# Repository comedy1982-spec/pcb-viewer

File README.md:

# AllinOneDesign

**요구사항 한 줄에서 시스템 다이어그램 → 회로 → PCB → 기구(하우징)까지, 브라우저 하나에서 AI와 함께 설계하는 단일 HTML 도구**입니다. 파일은 브라우저 안에서만 처리되며 서버로 전송되지 않습니다.

- 실행: `dist/index.html`을 브라우저로 엽니다 (3D·zip·엑셀 라이브러리만 CDN에서 불러오므로 인터넷 연결 필요).
- 사용 설명서: [docs/manual.html](docs/manual.html) · 기능 상세 노트(버전별): [docs/DETAILS.md](docs/DETAILS.md)
- 예제: SENSE-32, MCU DC 모터(MOTION-32 DEV), MCU BLDC 3상(MOTION-32 BLDC), AURIX TC364 인버터 — 첫 화면의 예제 칩으로 엽니다.

## 주요 기능

### 1. 단계별 설계 (신규 설계)
| 단계 | 하는 일 | 결과물 |
|---|---|---|
| **1 시스템 다이어그램** | 프로젝트 이름·요구사항을 적으면 AI가 분석하고, 빠진 필수 정보(전원·MCU·통신·기능·환경)는 **응답형 질문 카드**로 물어본 뒤 HW 블록 다이어그램을 그립니다. 블록·기능·인터페이스를 명령 또는 패널에서 편집합니다. | HW 블록 다이어그램 (SVG) |
| **2 회로** | 다이어그램을 **저가형 · 표준 · 확장형** 세 회로 안으로 풀어 BOM 참고가·부품 수·여유 MCU 핀·레귤레이터 손실·점수를 비교하고 하나를 고릅니다. 실제 부품 선정 · 넷리스트 · MCU 핀 배정 · 회로도가 만들어지며, **데이터시트 탭**에서 부품별 정리 페이지(HTML DB)를 봅니다. | 회로도(여러 시트) · 넷리스트 · BOM |
| **3 PCB** | 층 수(2–10) · 보드 크기(최소화/자동/직접) · 배치 전략을 고르면 자동 배치·배선합니다. 부품 끌어 옮기기·배선·비아·DRC·래츠네스트 편집, 내층을 포함한 **층별 보기**, 핀 스왑으로 회로와 함께 수정. | 배치·배선된 보드 (KiCad 저장) |
| **모터 파워 스테이지** | DC 모터 H-브리지(게이트 드라이버 ×2 + 외부 N-MOSFET ×4)·3상 인버터(×3 + ×6)를 전류 등급에 맞춰 FET 병렬·션트·전류 앰프·벌크·역전압 P-FET까지 회로로 생성, 트레이스 폭에 모터 전류 반영. | 회로도 · BOM |
| **부품 핀** | 라이브러리에 핀이 없으면 데이터시트 PDF를 올려 핀 표를 읽어 저장(pdf.js, 패키지별 표 선택, AI 모드 Claude 판독) — `datasheet <MPN>`, add part / replace, 라이브러리 버튼. | 핀 배열 → 회로 |
| **1 안전 목표** | ASIL ≠ QM이면 안전 목표(SG)를 고르고 위반 경로 블록에 태그, 구조 변형 3안(단일 MCU+외부 감시 · 메인+세이프티 MCU · ASIL 분해 2채널)을 DC·FTTI·원가로 비교해 적용, 규칙으로 검증(감지·독립 차단·FTTI·독립성·공통 원인). | SG 태그 · 검증 ✓/✗ |
| **4 기구 CAD** | 보드를 감싸는 보호 하우징을 Text-to-CAD로 설계합니다(시안 A 다이캐스팅·B 사출 스냅핏·C 압출 프로파일·D 하이브리드, 재질 6종·IP·진동·발열 조건, 구멍·글랜드·벤트·탭·리브·핀·각인, 둥근모따기/각모따기). 3D에서 요소를 **선택해 AI에게 지시**하고, 조립도·부품도(베이스/커버)·기구 BOM·SCAD/STL을 냅니다. | 하우징 3D · 도면 · BOM · SCAD |

기존 프로젝트(KiCad `.kicad_pcb`·회로도, PADS Logic 회로도, Gerber, 뷰어 JSON)도 같은 단계 표시줄로 오갑니다. 1단계는 보드에서 추출한 HW 블록 다이어그램입니다.

### 2. AI 설계 도우미
- 오른쪽 도킹 패널의 **설계 도우미**가 네 단계의 콘솔(시스템·회로도·배치/배선·Text-to-CAD)을 하나의 대화로 합칩니다. 결정론 모드는 문장을 규칙으로 명령으로 바꾸고, AI 모드는 Claude가 같은 명령을 골라 실행합니다.
- 설계를 바꾼 실행마다 **변경 요청 카드**가 붙습니다: 시스템·회로·PCB·HSIS·기구·BOM 영향, 변경 요약, 실행한 명령. **승인**하면 `CR-n` 리비전으로 기록되고, **되돌리기**는 그 실행만 정확히 되돌립니다.
- 기구 CAD에서는 3D나 형상 트리에서 요소를 고른 뒤(Shift/Ctrl 다중) "이거 M20으로 키우고 윗면은 R2"처럼 지시합니다.
- **등급 부품 자동 적용**: ASIL 프로젝트는 회로 생성 때 상용 부품을 핀 호환 차량용(AEC-Q100/Q101/Q200) 부품으로 바꾸고, `safety parts [--apply]`가 등급 미달·미상 부품과 대체품을 점검·일괄 교체합니다. 부품 레코드에 등급·온도·ASIL·FIT 필드(CSV·Claude 추정·API).
- **기능 안전(ASIL)**: 요구사항의 ASIL A~D를 읽어 시스템·블록 등급(배지·세이프 스테이트 경로·FFI 경계)을 다이어그램에 얹고, 등급별 권장 안전 메커니즘(전원 감시·외부 워치독·fault 리드백·SBC·이중 차단·리던던트 센서·2채널)을 블록으로 추가해 회로 부품(TPS3823 감시/워치독, 하이사이드 차단 스위치)까지 생성합니다. 회로·PCB 콘솔 `safety check`/`safety fmeda`가 등급별 회로 점검과 FIT·DC·SPFM·PMHF 추정을 내고 보고서·Excel·HSIS에 실립니다.
- **회로 해석(analyze)**: 전원 트리 · 디커플링 감사 · RC/LC·분압·LED 패턴 · 수동 소자 AC 주파수 응답 · DC 동작점(MNA) · IR drop · 신호 무결성 · 열 · EMC를 조회 명령으로 열어, 질문 모드의 Claude가 "필터 컷오프 얼마야?", "레일 전압 강하는?"에 계산값으로 답합니다.
- **아무 부품이나 추가**: "CC2420 추가해줘" → 라이브러리/Claude 추정의 핀 배열로 심볼을 만들고 전원·접지 자동 연결, 나머지 핀은 `connect`로, `apply`로 보드에(패키지 이름으로 풋프린트 생성).
- **보드 모양**: 사각형 외에 라운드·원형·타원·L자·T자·육각·팔각·다각형과 컷아웃(구멍) — 시작 카드에서 고르거나 `board shape …`/"원형 60mm로".
- **제품 프로필**: "EPS ECU 설계"처럼 제품만 적어도 표준 블록 구성(전원·SBC·락스텝 MCU·CAN-FD·인버터·페이즈 컷·센서 IF…)을 먼저 깔고, 블록별로 갈리는 것(타입·센서 IF·리던던시…)만 묻습니다. AI 모드는 어떤 제품이든, 규칙 모드는 EPS·BMS·BCM·인버터 템플릿.
- **로컬 AI**: claude.ai 밖(내려받은 파일·`npm run serve`)에서는 [Claude 허용] → 로컬 AI 설정에 API 키(또는 프록시)를 넣으면 같은 AI 모드가 Messages API로 동작합니다. `npm run serve:copilot`이면 API 키 없이 **GitHub Copilot** 구독(Copilot CLI 로그인)으로 동작합니다.
- **회로 보강 명령**: "HSIS 기준으로 테스트 포인트 전부 달아줘"(`tp`), "안 쓰는 핀 10k로 GND에"(`tie`), "전원 입력에 페라이트 비드"(`insert`), `add C --pins U1.12,GND`처럼 핀을 직접 지정 — AI 모드가 이 명령들로 풀어 실행하고 보드에 반영(`apply`)까지 합니다. TP는 HSIS 표의 TP 열·검사에 연결됩니다.
- **부품 교체(대화형)**: "U2를 AP2112K-3.3으로 바꿔줘"라고 하면 승인 부품 목록 → 내장 DB → Claude 추정 → 부품 API(Mouser·Nexar·사내 서버) 순으로 부품을 찾고, 핀 대응(이름·역할·번호)을 표로 확인받은 뒤 회로도·보드(풋프린트 자동 생성)·BOM·데이터시트·HSIS를 한 번에 바꿉니다. 머리글 **부품** 창에서 회사 승인 부품 목록(CSV/Excel)을 가져오고 추정 결과를 승인·내보냅니다.

### 3. 보기 · 분석
- **3D / TOP / BOTTOM / 층별(내층 포함) / 회로도**, 나란히 보기, 여러 보기를 격자로 띄우는 **새 창**(시스템 다이어그램·기구 3D·기구 도면·HSIS·시뮬레이션 포함, 메인 창과 연동).
- **지표 띠**: BOM 참고가, 가이드라인 점수, DRC·미배선, HSIS 정상/전체, 최고 Tj, 하우징 무게·IP — 누르면 해당 화면으로.
- **전체 보기**: 네 단계의 그림과 수치가 화살표로 이어진 한 화면, AI 바 포함.
- **시뮬레이션**: 전압 강하(IR drop), 신호 무결성, 열 분포, EMC/EMI, 회로 동작(MNA + 펌웨어 코시뮬레이션: LED·모터가 3D에서 움직임).
- **설계 가이드라인** 점검(회로·PCB 프리셋), DRC.

### 4. HSIS (HW/SW 인터페이스 사양)
- 엑셀 HSIS와 AUTOSAR ARXML을 읽어 **신호 표 · MCU 핀 맵 · 추적성(요구사항↔테스트) · 검사 결과 · 핀 추천(헝가리안 매칭) · MCAL 설정 · 테스트 케이스(SWE.6/SYS.4)**를 만들고 회로도·보드·펌웨어와 대조합니다.
- 보드에 HSIS가 없으면 MCU 핀과 넷으로 초안을 만듭니다.

### 5. 멀티보드 시스템
- 메인 + 센서 보드처럼 **보드 둘 이상을 커넥터로 잇는 제품**을 한 시스템으로 묶습니다. 머리글의 보드 선택 상자로 보드를 추가(파일·신규 설계·예제)하고 오갑니다.
- **시스템 연결** 탭: 보드·커넥터 짝으로 연결(케이블/B2B)을 만들고 핀을 번호·넷 이름·직접으로 매핑, 핀 수·짝 없는 핀·접지/전원/신호 충돌·레일 전압·차동 쌍 점검, 보드 연결도(SVG/PNG), 시스템 넷, 시스템 BOM(보드별 수량) → Excel·보고서.

### 6. 리비전 기록 · 비교
- 설계가 바뀌면 자동으로 리비전이 쌓이고(원인·단계·변경 요약 포함), 이름·단계(Proto~MP)·메모를 붙여 저장할 수 있습니다.
- **비교**: 요약 · 부품 · 배치 · 넷/핀 · **PCB 겹쳐 보기**(같음/A에만/B에만) · 다이어그램·계획 · HSIS · 기구. **원장** 보기는 리비전×영역 표.
- **복원**, 이력 JSON 내보내기/불러오기(Git에 함께 커밋).

### 7. 내보내기
- **프로젝트 저장 · 열기 · 이어서 하기**: 설계 중 어느 단계에서든 [저장](Ctrl+S)으로 전체 설계(모든 보드 · 요구사항 · 다이어그램 · 회로 안 · PCB · 기구 · HSIS, 열려 있던 단계)를 `.aod.json` 한 파일로 받고, [열기](Ctrl+O) · 첫 화면 · 파일 불러오기로 다시 엽니다. 작업은 브라우저에도 자동 저장돼, 새로 고침 뒤 첫 화면의 [이어서 하기]로 돌아옵니다.
- 회로도 교환: **PADS Logic ASCII**(.txt) 내보내기·가져오기, PADS Layout용 **PADS 넷리스트**(.asc), KiCad `.kicad_sch`. 회로도 파일만 넣으면 그 부품·넷으로 보드를 만들어 PCB 단계로 이어 갑니다.
- 그림: 2D 보드(층별)·회로도는 화면과 동일한 **SVG**, PNG, 시스템 다이어그램, 3D·기구 3D PNG, 기구 조립도·부품도, 모든 층 zip.
- 표: HSIS(시트별), BOM, 부품 배치, 넷리스트, 층 구성, 기구 BOM, 리비전 기록, 비교 결과 → **Excel**.
- **설계 보고서**: 항목을 골라 그림·표를 모두 담은 HTML 한 파일(브라우저 인쇄로 PDF). KiCad PCB/회로도 저장, OpenSCAD·STEP(AP214 솔리드 — SolidCraft·Fusion·SolidWorks·FreeCAD)·STL·HSIS CSV·MCAL 파일.

### 8. 실제 부품 데이터
- 부품 DB(제조사·사양·데이터시트 링크·참고 단가)와 MCU 핀 기능 DB(TC364DP, STM32F042), 부품당 한 레코드인 **데이터시트 DB**(원본 `datasheets/records/*.json` → 페이지 `datasheets/db/`, `npm run dsdb`; 회로 생성기의 후보 사양도 여기서 읽음).
- **부품 라이브러리**: 승인 부품 목록(CSV/Excel) · Claude 추정 · 부품 API 결과를 브라우저에 쌓아 두고 교체·데이터시트 탭에서 씁니다. 패키지 이름만으로 풋프린트(SOT-23-5, SOIC-14, QFN-24 4x4, DIP-8 …)를 만들어 보드에 올립니다.

## 화면 구성

```
┌ 머리: 프로젝트 · [전체] [1 시스템 · 2 회로 · 3 PCB · 4 기구] [HSIS] [시스템 연결] · 불러오기 · 내보내기 · 리비전 · 보기 전환 · 도우미 ┐
├ 지표 띠: BOM · 가이드라인 · DRC · HSIS · 최고 Tj · 시스템 연결 · 하우징                                                       ┤
├ 작업 공간 (단계마다 바뀜)                                            │ 도킹 패널: 설계 도우미 · 정보 · 시뮬레이션 · 데이터시트 ┤
│   레이어/보드 요약 · 3D/TOP/BOTTOM/층별/회로도 · 시스템 다이어그램 · 기구 CAD · HSIS │   (탭마다 새 창으로 뗄 수 있음)              │
└──────────────────────────────────────────────────────────────────┴──────────────────────────────────────────────┘
```

## 개발

```sh
npm run build     # src/ → dist/index.html (datasheets/db → dsdb.js 포함, Node 18+)
npm test          # 파서·회로도·시뮬레이션·HSIS·배치·배선·하우징·리비전·내보내기 테스트
npm run dsdb      # 데이터시트 HTML DB 번들 · npm run dsdb:init 초안 생성
npm run examples  # examples/ 다시 만들기 (python3 + openpyxl)
```

| 경로 | 내용 |
|---|---|
| `src/core/` | 보드 모델·파서(`pcb-core`), 편집(`pcbedit`), 자동 배치(`autoplace`), HW 아키텍처(`hwarch`), 시스템 다이어그램(`sysdiag`), 새 회로 설계(`newproj`), 하우징(`housing`), Text-to-CAD(`text2cad`), 가이드라인(`guide`), 리비전 스냅샷·비교(`revlog`), 멀티보드 시스템(`multiboard`), 부품 라이브러리·핀 대응(`partlib`), 풋프린트 생성(`fpgen`) |
| `src/route/autoroute.js` | 다층 자동 배선 |
| `src/sch/` | 회로도 파서·생성·편집 (KiCad, PADS Logic `pads.js`) |
| `src/sim/` | 전기·열·EMC 해석, MNA 회로 해석 |
| `src/hsis/` | HSIS 파서·검사·추적성, 핀 추천, MCAL, 테스트 케이스 생성 |
| `src/parts/` | 부품 DB, MCU 핀 DB, 데이터시트 DB 번들 |
| `src/fw/fw.js` | MCU 펌웨어 런타임 (샌드박스, 회로와 1 ms 코시뮬레이션) |
| `src/app/` | 화면: `viewer`(2D/3D), `newui`(단계·회로 안), `copilot`(도우미), `pcbui`·`pcbcli`(PCB 편집·CLI), `schui`·`schcli`, `mechui`(기구), `hsisui`, `simui`, `popui`(새 창), `exportui`, `revui`, `nextui`(지표·전체 보기·변경 요청·원장·분해), `iconui`, `mbui`(멀티보드), `partui`(부품 교체·라이브러리), `modeui`, `dsui`, `aimode` |
| `datasheets/records/` | 부품별 데이터시트 레코드(JSON, 원본) |
| `datasheets/db/` | 레코드에서 생성한 HTML 페이지 |
| `docs/` | 사용 설명서(`manual.html`), 기능 상세 노트(`DETAILS.md`), 화면 캡처(`img/`) |
| `test/` | `node --test` 테스트 |

모든 수치(열·진동·EMC·단가·하우징)는 초기 설계용 추정입니다. 양산 전에는 전문 도구와 시험으로 확인하세요.

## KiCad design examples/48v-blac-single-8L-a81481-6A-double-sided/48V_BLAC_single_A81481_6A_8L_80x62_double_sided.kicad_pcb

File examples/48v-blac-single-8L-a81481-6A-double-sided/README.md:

# 48 V BLAC 단일 채널 · A81481 · 6 A · 8층 80 × 62 mm (양면 배치)

[6 A 단면 예제(84 × 66)](../48v-blac-single-8L-a81481-6A/)와 같은 회로를 양면으로 배치한 보드입니다. 부품 113개 중 29개(전원 · MCU · 통신 · 센싱 쪽 패시브와 소형 IC)가 아랫면에 있고, FET · 게이트 드라이버 · 커넥터는 윗면에 있습니다. 면적은 단면 대비 −10.5 %입니다.

> A81481은 출시 전 부품이라 핀 배치가 **가정**입니다. 그대로 출도할 수 없습니다.

## 결과
- 미연결 0 · DRC 0 · 비아 전류 미달 없음
- 상 폭 PH_U 9.83 · PH_V 12.15 · PH_W 12.78 mm (필요 1.17 mm), 평면 온도 상승 +48 V +1.4 °C · GND +0.4 °C
- 미세 피치 IC 반대면 바로 아래에는 부품이 없습니다

## 더 작은 크기 (양면 · 시드 1)
78 × 62 미연결 1 · 80 × 60 미연결 2 · 78 × 60 미연결 2 · 76 × 62 미연결 3과 간격 오류 1 · 76 × 60 미연결 5 · 80 × 58 미연결 15.

## 만든 방법 (v1.136.0)
```
node scripts/pcbrun.cjs --plan examples/48v-blac-single-8L-a81481-6A-double-sided/plan.json --w 80 --h 62 --snap --kicad --shots \
  --cmds "board layers 8; board size 80 62 --anchor center; reset --strategy compact --both --seed 1; route; route --ai --agents --rules --noRoute --steps 12"
```
자동 배선 후 신호 2건이 남았고 오케스트레이션(규칙 처방)이 3단계에 이었습니다.

앱에서는 [파일 불러오기] → "예제: 48 V BLAC 단일 · 6 A 양면 80 × 62".

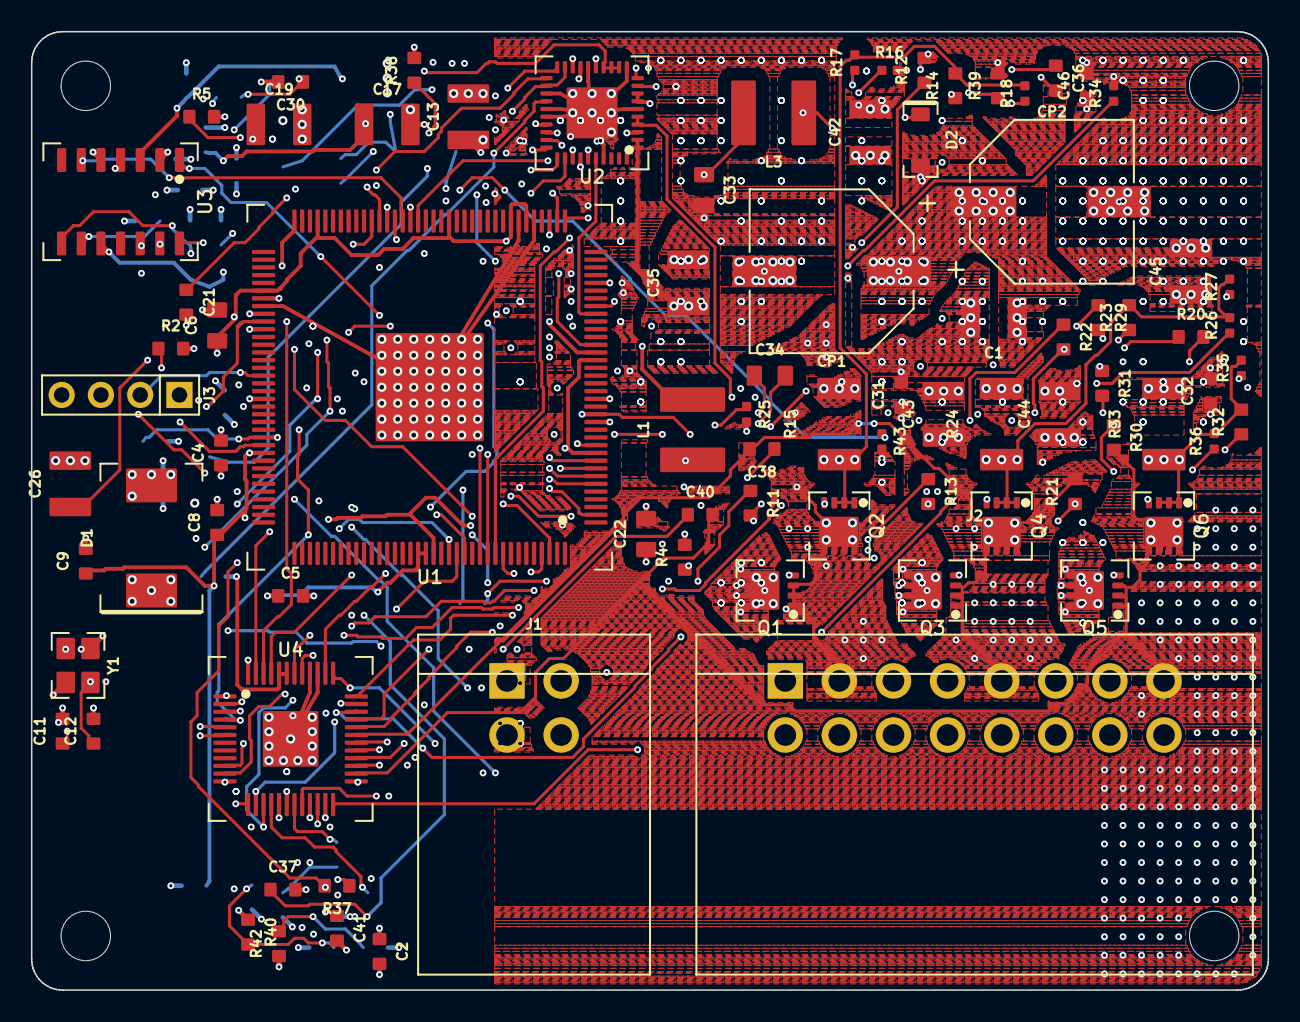
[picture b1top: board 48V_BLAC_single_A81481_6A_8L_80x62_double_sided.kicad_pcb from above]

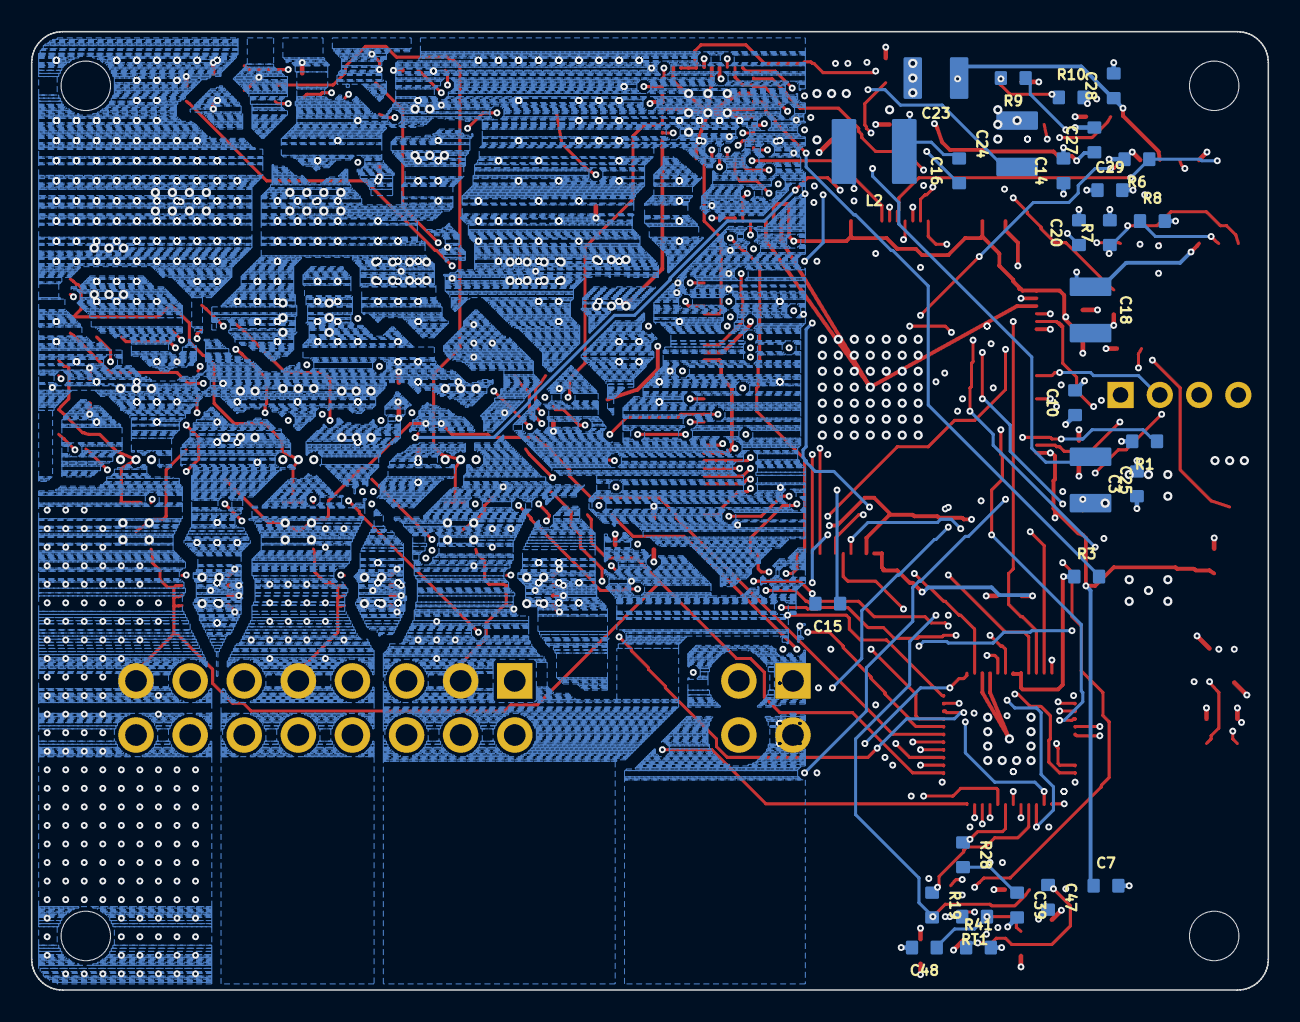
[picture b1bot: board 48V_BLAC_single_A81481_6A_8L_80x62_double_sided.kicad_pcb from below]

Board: 8 copper layers, 80.0 x 62.0 mm, 117 parts (29 on the bottom side), 95 nets.

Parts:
C1, C23, C24, C25, C26, C42, C43, C44, C45: 2.2µF; 1210
C2, C3, C4, C5, C7, C8, C10, C14, C15, C16, C20, C27, C28, C29, C31, C32, C46, C47, C48: 100nF; 0603
C6, C22, C33: 10µF; 0805
C9: 470nF; 0603
C11, C12: 12pF; 0603
C13, C35: 4.7µF; 1210
C17, C18: 10µF; 1210
C19: 22µF; 1210
C21: 1µF; 0603
C30: 4.7nF; 0603
C34: 1µF; 0805
C36, C38, C40: 68nF; 0603
C37, C39, C41: 1nF; 0603
CP1, CP2: 100µF; CP-SMD-10x10
D1: SMCJ58A; SMC
D2: PMEG10010ELR; SOD-123
H1, H2, H3, H4: MountingHole
J1: ECU-IN; MX150-2x2-RA
J2: ECU-OUT; MX150-2x8-RA
J3: DAP; HDR-1x4
L1: 22µH; IND-5x5
L2: 4.7µH; IND-5x5
L3: 100µH; IND-5x5
Q1, Q2, Q3, Q4, Q5, Q6: NVTFS6H850N; WDFN8-3.3-FET
R1, R2, R4, R5, R6, R7, R8, R12, R14, R21, R23, R30, R32, R38, R39, R42: 10kΩ; 0603
R3, R40: 100kΩ; 0603
R9, R10: 60.4Ω; 0603
R11, R13, R20, R22, R29, R31: 10Ω; 0603
R15, R24, R33: 10mΩ; 2010
R16, R17, R18, R25, R26, R27, R34, R35, R36: 0Ω; 0402
R19, R28, R37: 1kΩ; 0603
R41: 22kΩ; 0603
R43: 10kΩ; 0402
RT1: NTC 10k; 0603
U1: TC364DP; TQFP-144
U2: A81481; QFN-40
U3: TCAN1043HDRQ1; SOIC-14
U4: AMT49100; QFP-48-EP-7x7-P0.5
Y1: 20MHz; XTAL-3225

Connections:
+3V3: C3.1, C4.1, C5.1, C6.1, C10.1, C22.1, C29.1, J3.1 (3V3), R1.2, R2.2, R4.2, R5.2, R7.2, R38.2, R42.1, U1.23 (VEXT), U1.42 (VAREF1), U1.44 (VDDM), U1.52 (VEVRSB), U1.69 (VEXT), U1.78 (VEXT), U1.83 (VEXT), U1.125 (VEXT), U1.126 (VDDP3), U2.15 (VUC), U3.5 (VIO)
+5V: C23.1, C28.1, U2.17 (VLDOA), U3.3 (VCC)
+12V: C17.1, C18.1, C27.1, L1.2, U2.7 (VREG1), U2.8 (VIN2), U3.10 (VSUP)
+48V: C1.1, C2.1, C13.1, C14.1, C31.1, C32.1, C35.1, C42.1, C43.1, C44.1, C45.1, C46.1, CP1.1, CP2.1, D1.1 (K), J1.1 (BAT), Q1.5 (D), Q1.6 (D), Q1.7 (D), Q1.8 (D), Q1.9 (D), Q3.5 (D), Q3.6 (D), Q3.7 (D), Q3.8 (D), Q3.9 (D), Q5.5 (D), Q5.6 (D), Q5.7 (D), Q5.8 (D), Q5.9 (D), R3.1, R40.1, U2.1 (VIN), U2.2 (VIN), U4.43 (VBRG), U4.44 (VBB)
CANH: J1.2 (CAN_H), R9.1, U3.13 (CANH)
CANL: J1.4 (CAN_L), R10.2, U3.12 (CANL)
CAN_EN: R6.1, U1.58 (P33.2), U3.6 (EN)
CAN_ERR: R7.1, U1.142 (P10.3), U3.8 (~FAULT)
CAN_RX: U1.129 (P13.1), U3.4 (RXD)
CAN_SPLIT: C30.1, R9.2, R10.1
CAN_STB: U1.59 (P33.3), U3.14 (~STB)
CAN_TX: U1.11 (P00.0), U3.1 (TXD)
CAN_WAKE: R8.1, U3.9 (WAKE)
ESR0: R2.1, U1.98 (ESR0)
GND: C1.2, C2.2, C3.2, C4.2, C5.2, C6.2, C7.2, C8.2, C9.2, C10.2, C11.2, C12.2, C13.2, C14.2, C17.2, C18.2, C19.2, C20.2, C21.2, C22.2, C23.2, C24.2, C25.2, C26.2, C27.2, C28.2, C29.2, C30.2, C31.2, C32.2, C33.2, C35.2, C37.2, C39.2, C41.2, C42.2, C43.2, C44.2, C45.2, C46.2, C47.2, C48.2, CP1.2, CP2.2, D1.2 (A), D2.2 (A), J1.3 (GND), J3.4 (GND), R6.2, R8.2, R15.2, R16.2, R24.2, R25.2, R33.2, R34.2, R39.2, R41.2, R43.2, RT1.2, U1.41 (VAGND1), U1.43 (VSSM), U1.80 (VSS), U1.145 (VSS (노출 패드)), U2.6 (PGND1), U2.11 (PGND2), U2.16 (VUCSEL), U2.23 (AGND), U2.25 (ENCAN), U2.26 (EN), U2.37 (GND), U2.41 (GND (노출 패드)), U3.2 (GND), U4.39 (GND), U4.40 (GND), U4.49 (PAD), Y1.2, Y1.4
PH_CP1: C34.1, U4.42 (CP1)
PH_CP2: C34.2, U4.41 (CP2)
PH_DIAG: R38.1, U1.2 (P02.1), U4.6 (DIAG)
PH_EN: R39.1, U1.60 (P33.4), U4.46 (ENABLE)
PH_INH_U: U1.131 (P13.3), U4.45 (HA)
PH_INH_V: U1.130 (P13.2), U4.2 (HB)
PH_INH_W: U1.14 (P00.3), U4.4 (HC)
PH_INL_U: U1.9 (P02.8), U4.1 (LA)
PH_INL_V: U1.136 (P11.8), U4.3 (LB)
PH_INL_W: U1.17 (P00.6), U4.5 (LC)
PH_ISNS_U: C37.1, R19.2, U1.29 (AN34)
PH_ISNS_U_AMP: R19.1, U4.16 (CS1O)
PH_ISNS_V: C39.1, R28.2, U1.32 (AN28)
PH_ISNS_V_AMP: R28.1, U4.19 (CS2O)
PH_ISNS_W: C41.1, R37.2, U1.37 (AN21)
PH_ISNS_W_AMP: R37.1, U4.22 (CS3O)
PH_LX: D2.1 (K), L3.1, U4.48 (LX)
PH_RESETN: R43.1, U1.61 (P33.5), U4.47 (RESETn)
PH_SCK: U1.8 (P02.7), U4.12 (SCK)
PH_SDI: U1.7 (P02.6), U4.11 (SDI)
PH_SDO: U1.6 (P02.5), U4.10 (SDO)
PH_STRN: U1.62 (P33.6), U4.13 (STRn)
PH_U: C36.2, J2.2 (U), Q1.1 (S), Q1.2 (S), Q1.3 (S), Q2.5 (D), Q2.6 (D), Q2.7 (D), Q2.8 (D), Q2.9 (D), R12.2, U4.36 (SA)
PH_U_HG: Q1.4 (G), R11.2, R12.1
PH_U_HO: R11.1, U4.37 (GHA)
PH_U_LG: Q2.4 (G), R13.2, R14.1
PH_U_LO: R13.1, U4.34 (GLA)
PH_U_LSS: R18.1, U4.33 (LSSA)
PH_U_SNS: Q2.1 (S), Q2.2 (S), Q2.3 (S), R14.2, R15.1, R17.2, R18.2
PH_U_SNSM: R16.1, U4.15 (CS1M)
PH_U_SNSP: R17.1, U4.14 (CS1P)
PH_U_VB: C36.1, U4.35 (CA)
PH_V: C38.2, J2.5 (V), Q3.1 (S), Q3.2 (S), Q3.3 (S), Q4.5 (D), Q4.6 (D), Q4.7 (D), Q4.8 (D), Q4.9 (D), R21.2, U4.31 (SB)
PH_VREG: C33.1, L3.2, U4.38 (VREG)
PH_V_HG: Q3.4 (G), R20.2, R21.1
PH_V_HO: R20.1, U4.32 (GHB)
PH_V_LG: Q4.4 (G), R22.2, R23.1
PH_V_LO: R22.1, U4.29 (GLB)
PH_V_LSS: R27.1, U4.28 (LSSB)
PH_V_SNS: Q4.1 (S), Q4.2 (S), Q4.3 (S), R23.2, R24.1, R26.2, R27.2
PH_V_SNSM: R25.1, U4.18 (CS2M)
PH_V_SNSP: R26.1, U4.17 (CS2P)
PH_V_VB: C38.1, U4.30 (CB)
PH_W: C40.2, J2.8 (W), Q5.1 (S), Q5.2 (S), Q5.3 (S), Q6.5 (D), Q6.6 (D), Q6.7 (D), Q6.8 (D), Q6.9 (D), R30.2, U4.26 (SC)
PH_W_HG: Q5.4 (G), R29.2, R30.1
PH_W_HO: R29.1, U4.27 (GHC)
PH_W_LG: Q6.4 (G), R31.2, R32.1
PH_W_LO: R31.1, U4.24 (GLC)
PH_W_LSS: R36.1, U4.23 (LSSC)
PH_W_SNS: Q6.1 (S), Q6.2 (S), Q6.3 (S), R32.2, R33.1, R35.2, R36.2
PH_W_SNSM: R34.1, U4.21 (CS3M)
PH_W_SNSP: R35.1, U4.20 (CS3P)
PH_W_VB: C40.1, U4.25 (CC)
PMIC_BOOT1: C15.1, U2.3 (BOOT1)
PMIC_BOOT2: C16.1, U2.9 (BOOT2)
PMIC_DIAG: U1.28 (AN35), U2.36 (DIAG)
PMIC_ENBAT: R3.2, U2.24 (ENBAT)
PMIC_FFN: R4.1, U1.15 (P00.4), U2.28 (FFn)
PMIC_LX1: C15.2, L1.1, U2.4 (LX1), U2.5 (LX1)
PMIC_LX2: C16.2, L2.1, U2.10 (LX2)
PMIC_POE: U1.24 (P40.9/AN39), U2.29 (POE)
PMIC_SCL: U1.134 (P11.6), U2.32 (SCK)
PMIC_SCS: U1.56 (P33.0), U2.35 (STRn)
PMIC_SDI: U1.135 (P11.9), U2.33 (SDI)
PMIC_SDO: U1.133 (P11.3), U2.34 (SDO)
PMIC_VCC: C21.1, U2.19 (VLDOBSEL), U2.22 (VCC)
PMIC_VREG2: C19.1, C20.1, L2.2, U2.12 (VREG2), U2.13 (VREGLDO), U2.14 (VUCIN)
PMIC_WDF: R5.1, U1.141 (P10.2), U2.30 (WD_Fn)
PORST: R1.1, U1.97 (PORST), U2.27 (NPOR)
TCK: J3.3 (TCK), U1.92 (TCK)
TEMP: C48.1, R42.2, RT1.1, U1.39 (AN17)
TMS: J3.2 (TMS), U1.89 (TMS)
V5P1: C25.1, U2.20 (VLDOP1)
V5P2: C26.1, U2.21 (VLDOP2)
V5_AON: C24.1, U2.18 (VLDOB)
VDD: C7.1, C8.1, C9.1, U1.10 (VDD), U1.22 (VDD), U1.72 (VDD), U1.79 (VDD), U1.99 (VDD), U1.127 (VDD)
VMON: C47.1, R40.2, R41.1, U1.38 (AN20)
WDI: U1.57 (P33.1), U2.31 (WDIN)
XTAL1: C11.1, U1.81 (XTAL1), Y1.1
XTAL2: C12.1, U1.82 (XTAL2), Y1.3

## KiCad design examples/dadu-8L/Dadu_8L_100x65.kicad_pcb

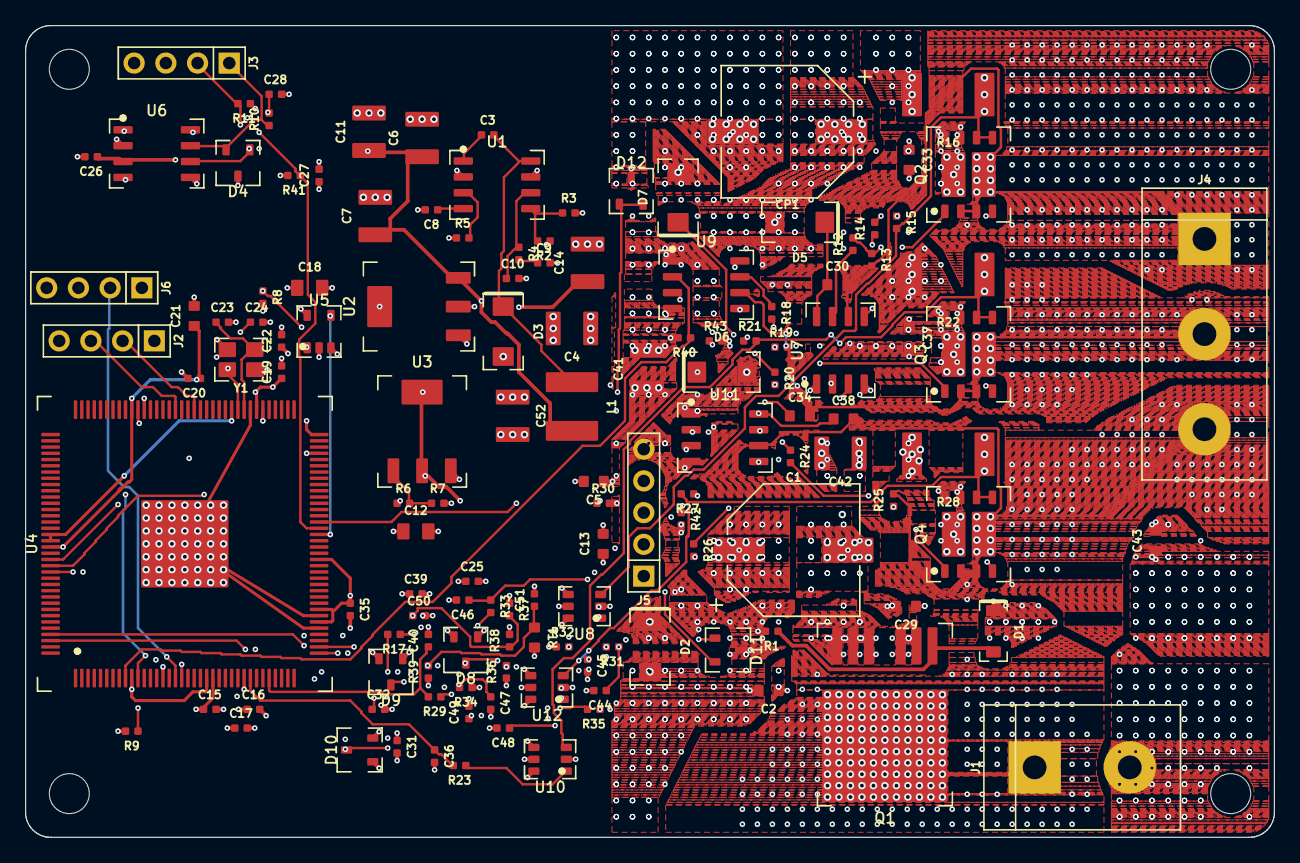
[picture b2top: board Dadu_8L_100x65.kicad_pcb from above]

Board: 8 copper layers, 100.0 x 65.0 mm, 137 parts (0 on the bottom side), 70 nets.

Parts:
C1: 470µF; CP-SMD-10x10
C2, C5, C43: 100nF; 0603
C3, C15, C16, C17, C19, C20, C22, C25, C26, C27, C31, C35, C39, C50, C51: 100nF; 0402
C4, C11, C14, C52: 10µF; 1210
C6, C7: 22µF; 1210
C8: 10nF; 0402
C9: 3.3nF; 0402
C10: 47pF; 0402
C12, C18: 10µF; 0805
C13, C29, C30, C33, C34, C37, C38: 1µF; 0603
C21: 470nF; 0603
C23, C24: 12pF; 0402
C28: 4.7nF; 0402
C32, C36, C40, C44, C45, C46, C47, C48, C49: 1nF; 0402
C41, C42: 2.2µF; 1210
CP1: 470µF; CP-SMD-10x10
D1: BZT52C12; SOD-123
D2: SMAJ15A; SMA
D3: MBRA340T3G; SMA
D4, D11, D12: PESD1CAN; SOT-23
D5, D6, D7: ES1D; SMA
D8, D9, D10: BAT54S; SOT-23
H1, H2, H3, H4: MountingHole
J1: 12V 입력; TERM-2-7.62
J2: DAP; HDR-1x4
J3: CAN; HDR-1x4
J4: 모터 상; TERM-3-7.62
J5: 홀; HDR-1x5
J6: UART; HDR-1x4
L1: 10µH; IND-5x5
Q1: IPB180P04P4L-02; TO-263-7
Q2, Q3, Q4: IAUC60N04S6N050H; TDSON-8-2FET
R1, R3, R8, R9, R13, R15, R19, R21, R25, R27, R30, R39, R40, R41, R42, R43: 10kΩ; 0402
R2: 52.3kΩ; 0402
R4: 76.8kΩ; 0402
R5, R37: 100kΩ; 0402
R6: 240Ω; 0402
R7: 1.5kΩ; 0402
R10, R11: 60.4Ω; 0402
R12, R14, R18, R20, R24, R26: 10Ω; 0402
R16, R22, R28: 2mΩ; 2512
R17, R23, R29, R31, R33, R35: 1kΩ; 0402
R32, R34, R36: 4.7kΩ; 0402
R38: 22kΩ; 0402
RT1: NTC 10k; 0603
U1: TPS54331; SOIC-8
U2: AMS1117-3.3; SOT-223
U3: LM317; SOT-223
U4: TC364DP; TQFP-144
U5: TPS3823-33; SOT-23-5
U6: TLE9251V; SOIC-8
U7, U9, U11: IR2104S; SOIC-8
U8, U10, U12: INA181A2-Q1; SOT-23-6
Y1: 20MHz; XTAL-3225

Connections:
+3V3: C12.1, C15.1, C16.1, C17.1, C18.1, C22.1, C25.1, C27.1, C31.1, C35.1, C39.1, D8.2 (K2), D9.2 (K2), D10.2 (K2), J2.1 (3V3), J6.4 (3V3), R8.2, R9.2, R32.1, R34.1, R36.1, R39.1, R41.2, U2.2 (VOUT), U2.4 (VOUT), U4.23 (VEXT), U4.42 (VAREF1), U4.44 (VDDM), U4.52 (VEVRSB), U4.69 (VEXT), U4.78 (VEXT), U4.83 (VEXT), U4.125 (VEXT), U4.126 (VDDP3), U5.3 (MR), U5.5 (VDD), U6.5 (VIO), U8.6 (VS), U10.6 (VS), U12.6 (VS)
+5V: C6.1, C7.1, C11.1, C26.1, L1.2, R2.1, U2.3 (VIN), U6.3 (VCC)
+9V: C14.1, J5.1 (9V), R6.1, U3.2 (VOUT), U3.4 (VOUT)
+12V: C1.1, C2.1, C4.1, C5.1, C13.1, C29.1, C33.1, C37.1, C41.1, C42.1, C43.1, C52.1, CP1.1, D1.1 (K), D2.1 (K), D5.2 (A), D6.2 (A), D7.2 (A), Q1.2 (S), Q1.3 (S), Q1.5 (S), Q1.6 (S), Q1.7 (S), Q2.7 (BAT), Q2.8 (BAT), Q2.9 (BAT), Q3.7 (BAT), Q3.8 (BAT), Q3.9 (BAT), Q4.7 (BAT), Q4.8 (BAT), Q4.9 (BAT), R5.1, R37.1, U1.2 (VIN), U3.3 (VIN), U7.1 (VCC), U9.1 (VCC), U11.1 (VCC)
BUCK_BOOT: C3.1, U1.1 (BOOT)
BUCK_COMP: C10.1, R4.1, U1.6 (COMP)
BUCK_EN: R5.2, U1.3 (EN)
BUCK_FB: R2.2, R3.1, U1.5 (VSENSE)
BUCK_RC: C9.1, R4.2
BUCK_SS: C8.1, U1.4 (SS)
BUCK_SW: C3.2, D3.1 (K), L1.1, U1.8 (PH)
CANH: D4.2 (CANH), J3.1 (CANH), R10.1, U6.7 (CANH)
CANL: D4.1 (CANL), J3.2 (CANL), R11.2, U6.6 (CANL)
CAN_RX: U4.129 (P13.1), U6.4 (RxD)
CAN_SPLIT: C28.1, R10.2, R11.1
CAN_STB: R41.1, U4.57 (P33.1), U6.8 (STB)
CAN_TX: U4.11 (P00.0), U6.1 (TxD)
DBG_RX: J6.2 (RX), U4.17 (P00.6)
DBG_TX: J6.1 (TX), U4.18 (P00.7)
ESR0: R9.1, U4.98 (ESR0)
GND: C1.2, C2.2, C4.2, C5.2, C6.2, C7.2, C8.2, C9.2, C10.2, C11.2, C12.2, C13.2, C14.2, C15.2, C16.2, C17.2, C18.2, C19.2, C20.2, C21.2, C22.2, C23.2, C24.2, C25.2, C26.2, C27.2, C28.2, C29.2, C31.2, C32.2, C33.2, C35.2, C36.2, C37.2, C39.2, C40.2, C41.2, C42.2, C43.2, C44.2, C45.2, C46.2, C47.2, C48.2, C49.2, C50.2, C51.2, C52.2, CP1.2, D2.2 (A), D3.2 (A), D4.3 (GND), D8.1 (A1), D9.1 (A1), D10.1 (A1), D11.3 (K), D12.3 (K), J1.2 (GND), J2.4 (GND), J3.3 (GND), J5.5 (GND), J6.3 (GND), R1.2, R3.2, R7.2, R16.2, R22.2, R28.2, R30.2, R38.2, R40.2, R42.2, R43.2, RT1.2, U1.7 (GND), U2.1 (GND), U4.41 (VAGND1), U4.43 (VSSM), U4.80 (VSS), U4.145 (VSS (노출 패드)), U5.2 (GND), U6.2 (GND), U7.4 (COM), U8.2 (GND), U8.4 (IN−), U8.5 (REF), U9.4 (COM), U10.2 (GND), U10.4 (IN−), U10.5 (REF), U11.4 (COM), U12.2 (GND), U12.4 (IN−), U12.5 (REF), Y1.2, Y1.4
LDO_ADJ: R6.2, R7.1, U3.1 (ADJ)
PH_EN: R30.1, U4.58 (P33.2), U7.3 (nSD), U9.3 (nSD), U11.3 (nSD)
PH_HALL_A: C45.1, D8.3 (K1/A2), R31.2, R32.2, U4.15 (P00.4)
PH_HALL_A_IN: C44.1, D11.1 (K1), J5.2 (H1), R31.1
PH_HALL_B: C47.1, D9.3 (K1/A2), R33.2, R34.2, U4.141 (P10.2)
PH_HALL_B_IN: C46.1, D11.2 (K2), J5.3 (H2), R33.1
PH_HALL_C: C49.1, D10.3 (K1/A2), R35.2, R36.2, U4.142 (P10.3)
PH_HALL_C_IN: C48.1, D12.1 (K1), D12.2 (K2), J5.4 (H3), R35.1
PH_IN_U: R43.1, U4.131 (P13.3), U7.2 (IN)
PH_IN_V: R40.1, U4.9 (P02.8), U9.2 (IN)
PH_IN_W: R42.1, U4.130 (P13.2), U11.2 (IN)
PH_ISNS_U: C32.1, R17.2, U4.28 (AN35)
PH_ISNS_U_AMP: R17.1, U8.1 (OUT)
PH_ISNS_V: C36.1, R23.2, U4.29 (AN34)
PH_ISNS_V_AMP: R23.1, U10.1 (OUT)
PH_ISNS_W: C40.1, R29.2, U4.32 (AN28)
PH_ISNS_W_AMP: R29.1, U12.1 (OUT)
PH_U: C30.2, J4.1 (U), Q2.2 (PH), Q2.3 (PH), Q2.10 (PH), R13.2, U7.6 (VS)
PH_U_HG: Q2.1 (G_HS), R12.2, R13.1
PH_U_HO: R12.1, U7.7 (HO)
PH_U_LG: Q2.4 (G_LS), R14.2, R15.1
PH_U_LO: R14.1, U7.5 (LO)
PH_U_SNS: Q2.5 (GND), Q2.6 (GND), R15.2, R16.1, U8.3 (IN+)
PH_U_VB: C30.1, D5.1 (K), U7.8 (VB)
PH_V: C34.2, J4.2 (V), Q3.2 (PH), Q3.3 (PH), Q3.10 (PH), R19.2, U9.6 (VS)
PH_V_HG: Q3.1 (G_HS), R18.2, R19.1
PH_V_HO: R18.1, U9.7 (HO)
PH_V_LG: Q3.4 (G_LS), R20.2, R21.1
PH_V_LO: R20.1, U9.5 (LO)
PH_V_SNS: Q3.5 (GND), Q3.6 (GND), R21.2, R22.1, U10.3 (IN+)
PH_V_VB: C34.1, D6.1 (K), U9.8 (VB)
PH_W: C38.2, J4.3 (W), Q4.2 (PH), Q4.3 (PH), Q4.10 (PH), R25.2, U11.6 (VS)
PH_W_HG: Q4.1 (G_HS), R24.2, R25.1
PH_W_HO: R24.1, U11.7 (HO)
PH_W_LG: Q4.4 (G_LS), R26.2, R27.1
PH_W_LO: R26.1, U11.5 (LO)
PH_W_SNS: Q4.5 (GND), Q4.6 (GND), R27.2, R28.1, U12.3 (IN+)
PH_W_VB: C38.1, D7.1 (K), U11.8 (VB)
PORST: R8.1, U4.97 (PORST), U5.1 (RESET)
TCK: J2.3 (TCK), U4.92 (TCK)
TEMP: C51.1, R39.2, RT1.1, U4.38 (AN20)
TMS: J2.2 (TMS), U4.89 (TMS)
VDD: C19.1, C20.1, C21.1, U4.10 (VDD), U4.22 (VDD), U4.72 (VDD), U4.79 (VDD), U4.99 (VDD), U4.127 (VDD)
VIN_PG: D1.2 (A), Q1.1 (G), R1.1
VIN_RAW: J1.1 (+), Q1.4 (D)
VMON: C50.1, R37.2, R38.1, U4.37 (AN21)
WDI: U4.56 (P33.0), U5.4 (WDI)
XTAL1: C23.1, U4.81 (XTAL1), Y1.1
XTAL2: C24.1, U4.82 (XTAL2), Y1.3

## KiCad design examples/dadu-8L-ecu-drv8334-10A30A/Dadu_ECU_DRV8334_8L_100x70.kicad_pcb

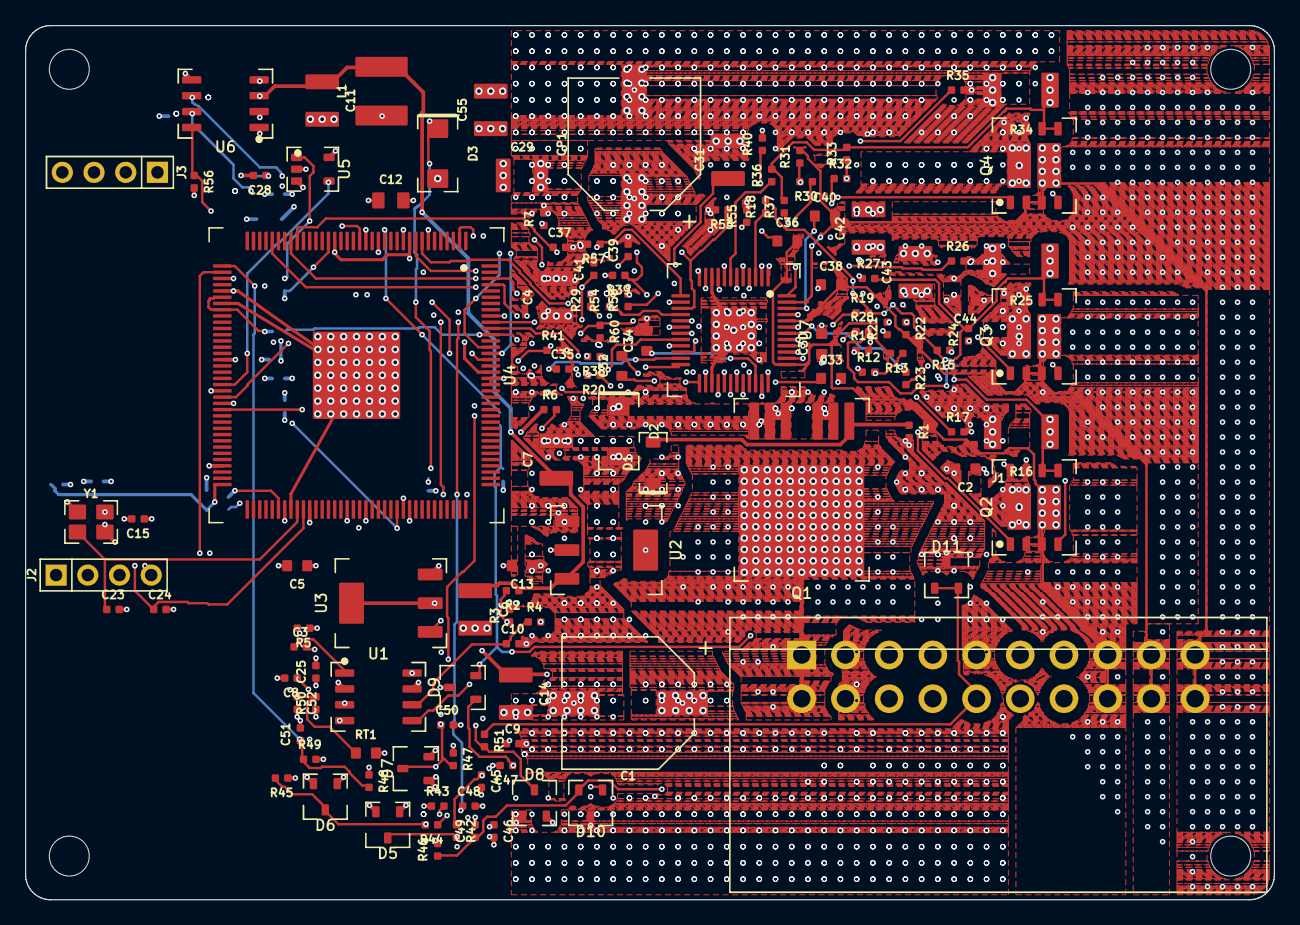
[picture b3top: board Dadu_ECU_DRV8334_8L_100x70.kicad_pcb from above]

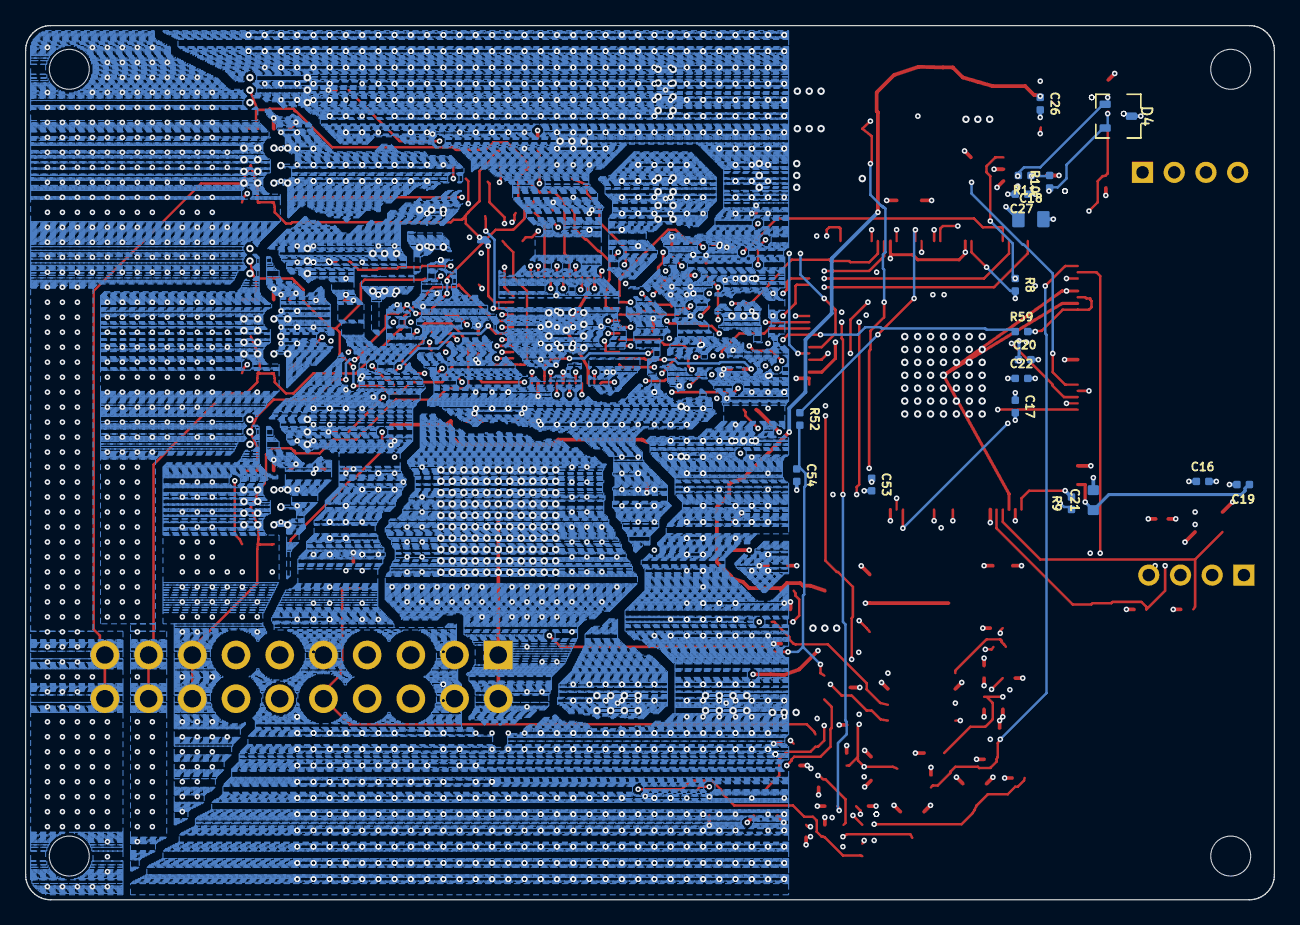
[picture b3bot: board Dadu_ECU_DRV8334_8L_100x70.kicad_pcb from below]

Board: 8 copper layers, 100.0 x 70.0 mm, 148 parts (18 on the bottom side), 98 nets.

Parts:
C1: 470µF; CP-SMD-10x10
C2, C5, C44: 100nF; 0603
C3, C15, C16, C17, C19, C20, C22, C25, C26, C27, C35, C51, C52: 100nF; 0402
C4, C11, C14, C29, C31, C55: 10µF; 1210
C6, C7: 22µF; 1210
C8, C53: 10nF; 0402
C9: 3.3nF; 0402
C10: 47pF; 0402
C12, C18: 10µF; 0805
C13, C30, C32, C33, C34, C36, C38, C40: 1µF; 0603
C21: 470nF; 0603
C23, C24: 12pF; 0402
C28: 4.7nF; 0402
C37, C39, C41: 470pF; 0402
C42, C43: 2.2µF; 1210
C45, C46, C47, C48, C49, C50, C54: 1nF; 0402
CP1: 470µF; CP-SMD-10x10
D1: BZT52C12; SOD-123
D2: SMAJ15A; SMA
D3: MBRA340T3G; SMA
D4, D9, D10, D11: PESD1CAN; SOT-23
D5, D6, D7, D8: BAT54S; SOT-23
H1, H2, H3, H4: MountingHole
J1: ECU; MX150-2x10-RA
J2: DAP; HDR-1x4
J3: UART; HDR-1x4
L1: 10µH; IND-5x5
Q1: IPB180P04P4L-02; TO-263-7
Q2, Q3, Q4: IAUC60N04S6N050H; TDSON-8-2FET
R1, R3, R8, R9, R13, R15, R22, R24, R31, R33, R39, R40, R41, R50, R53, R54, R55, R56, R57, R58, R59, R60: 10kΩ; 0402
R2: 52.3kΩ; 0402
R4: 76.8kΩ; 0402
R5, R48: 100kΩ; 0402
R6: 240Ω; 0402
R7: 1.5kΩ; 0402
R10, R11: 60.4Ω; 0402
R12, R14, R21, R23, R30, R32: 10Ω; 0402
R16, R25, R34: 2mΩ; 2010
R17, R18, R19, R26, R27, R28, R35, R36, R37: 0Ω; 0402
R20, R29, R38: 160Ω; 0402
R42, R44, R46, R51: 1kΩ; 0402
R43, R45, R47: 4.7kΩ; 0402
R49: 22kΩ; 0402
R52: 2.7kΩ; 0402
RT1: NTC 10k; 0603
U1: TPS54331; SOIC-8
U2: AMS1117-3.3; SOT-223
U3: LM317; SOT-223
U4: TC364DP; TQFP-144
U5: TPS3823-33; SOT-23-5
U6: TLE9251V; SOIC-8
U7: DRV8334-Q1; QFP-48-EP-7x7-P0.5
Y1: 20MHz; XTAL-3225

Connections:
+3V3: C12.1, C15.1, C16.1, C17.1, C18.1, C22.1, C25.1, C27.1, C35.1, D5.2 (K2), D6.2 (K2), D7.2 (K2), D8.2 (K2), J2.1 (3V3), J3.4 (3V3), R8.2, R9.2, R39.2, R40.2, R43.1, R45.1, R47.1, R50.1, R56.2, R59.2, U2.2 (VOUT), U2.4 (VOUT), U4.23 (VEXT), U4.42 (VAREF1), U4.44 (VDDM), U4.52 (VEVRSB), U4.69 (VEXT), U4.78 (VEXT), U4.83 (VEXT), U4.125 (VEXT), U4.126 (VDDP3), U5.3 (MR), U5.5 (VDD), U6.5 (VIO), U7.23
+5V: C6.1, C7.1, C11.1, C26.1, L1.2, R2.1, U2.3 (VIN), U6.3 (VCC)
+9V: C14.1, J1.3 (9V), R6.1, U3.2 (VOUT), U3.4 (VOUT)
+12V: C1.1, C2.1, C4.1, C5.1, C13.1, C29.1, C30.1, C34.2, C42.1, C43.1, C44.1, C55.1, CP1.1, D1.1 (K), D2.1 (K), Q1.2 (S), Q1.3 (S), Q1.5 (S), Q1.6 (S), Q1.7 (S), Q2.7 (BAT), Q2.8 (BAT), Q2.9 (BAT), Q3.7 (BAT), Q3.8 (BAT), Q3.9 (BAT), Q4.7 (BAT), Q4.8 (BAT), Q4.9 (BAT), R5.1, R48.1, U1.2 (VIN), U3.3 (VIN), U7.31, U7.35
BUCK_BOOT: C3.1, U1.1 (BOOT)
BUCK_COMP: C10.1, R4.1, U1.6 (COMP)
BUCK_EN: R5.2, U1.3 (EN)
BUCK_FB: R2.2, R3.1, U1.5 (VSENSE)
BUCK_RC: C9.1, R4.2
BUCK_SS: C8.1, U1.4 (SS)
BUCK_SW: C3.2, D3.1 (K), L1.1, U1.8 (PH)
CANH: D4.2 (CANH), J1.7 (CAN_H), R10.1, U6.7 (CANH)
CANL: D4.1 (CANL), J1.17 (CAN_L), R11.2, U6.6 (CANL)
CAN_RX: U4.129 (P13.1), U6.4 (RxD)
CAN_SPLIT: C28.1, R10.2, R11.1
CAN_STB: R56.1, U4.57 (P33.1), U6.8 (STB)
CAN_TX: U4.11 (P00.0), U6.1 (TxD)
DBG_RX: J3.2 (RX), U4.17 (P00.6)
DBG_TX: J3.1 (TX), U4.18 (P00.7)
ESR0: R9.1, U4.98 (ESR0)
GND: C1.2, C2.2, C4.2, C5.2, C6.2, C7.2, C8.2, C9.2, C10.2, C11.2, C12.2, C13.2, C14.2, C15.2, C16.2, C17.2, C18.2, C19.2, C20.2, C21.2, C22.2, C23.2, C24.2, C25.2, C26.2, C27.2, C28.2, C29.2, C30.2, C31.2, C35.2, C37.2, C39.2, C41.2, C42.2, C43.2, C44.2, C45.2, C46.2, C47.2, C48.2, C49.2, C50.2, C51.2, C52.2, C53.2, C54.2, C55.2, CP1.2, D2.2 (A), D3.2 (A), D4.3 (GND), D5.1 (A1), D6.1 (A1), D7.1 (A1), D8.1 (A1), D9.3 (K), D10.3 (K), D11.3 (K), J1.2 (GND), J1.5 (HALL_GND), J1.12 (GND), J2.4 (GND), J3.3 (GND), R1.2, R3.2, R7.2, R16.2, R17.2, R25.2, R26.2, R34.2, R35.2, R41.2, R49.2, R53.2, R54.2, R55.2, R57.2, R58.2, R60.2, RT1.2, U1.7 (GND), U2.1 (GND), U4.41 (VAGND1), U4.43 (VSSM), U4.80 (VSS), U4.145 (VSS (노출 패드)), U5.2 (GND), U6.2 (GND), U7.10, U7.27, U7.49, Y1.2, Y1.4
LDO_ADJ: R6.2, R7.1, U3.1 (ADJ)
PH_CPH: C32.1, U7.29
PH_CPL: C32.2, U7.28
PH_CPTH: C33.1, U7.33
PH_CPTL: C33.2, U7.32
PH_DRVOFF: R40.1, U4.58 (P33.2), U7.9
PH_GVDD: C31.1, U7.30
PH_HALL_A: C46.1, D5.3 (K1/A2), R42.2, R43.2, U4.141 (P10.2)
PH_HALL_A_IN: C45.1, D10.1 (K1), J1.13 (HALL_U), R42.1
PH_HALL_B: C48.1, D6.3 (K1/A2), R44.2, R45.2, U4.142 (P10.3)
PH_HALL_B_IN: C47.1, D9.1 (K1), J1.4 (HALL_V), R44.1
PH_HALL_C: C50.1, D7.3 (K1/A2), R46.2, R47.2, U4.2 (P02.1)
PH_HALL_C_IN: C49.1, D10.2 (K2), J1.14 (HALL_W), R46.1
PH_INH_U: R58.1, U4.131 (P13.3), U7.11
PH_INH_V: R57.1, U4.130 (P13.2), U7.13
PH_INH_W: R53.1, U4.7 (P02.6), U7.15
PH_INL_U: R55.1, U4.9 (P02.8), U7.12
PH_INL_V: R60.1, U4.136 (P11.8), U7.14
PH_INL_W: R54.1, U4.8 (P02.7), U7.16
PH_ISNS_U: C37.1, R20.2, U4.28 (AN35)
PH_ISNS_U_AMP: R20.1, U7.26
PH_ISNS_V: C39.1, R29.2, U4.29 (AN34)
PH_ISNS_V_AMP: R29.1, U7.25
PH_ISNS_W: C41.1, R38.2, U4.32 (AN28)
PH_ISNS_W_AMP: R38.1, U7.24
PH_NFAULT: R39.1, U4.15 (P00.4), U7.22
PH_NSCS: U4.60 (P33.4), U7.20
PH_NSLEEP: R41.1, U4.59 (P33.3), U7.21
PH_SCK: U4.134 (P11.6), U7.19
PH_SDI: U4.135 (P11.9), U7.18
PH_SDO: R59.1, U4.133 (P11.3), U7.17
PH_U: C36.2, J1.8 (U), J1.18 (U), Q2.2 (PH), Q2.3 (PH), Q2.10 (PH), R13.2, U7.37
PH_U_HG: Q2.1 (G_HS), R12.2, R13.1
PH_U_HO: R12.1, U7.38
PH_U_LG: Q2.4 (G_LS), R14.2, R15.1
PH_U_LO: R14.1, U7.39
PH_U_LSS: R19.1, U7.40
PH_U_SNS: Q2.5 (GND), Q2.6 (GND), R15.2, R16.1, R18.2, R19.2
PH_U_SNSM: R17.1, U7.4
PH_U_SNSP: R18.1, U7.3
PH_U_VB: C36.1, U7.36
PH_V: C38.2, J1.9 (V), J1.19 (V), Q3.2 (PH), Q3.3 (PH), Q3.10 (PH), R22.2, U7.44
PH_VCP: C34.1, U7.34
PH_V_HG: Q3.1 (G_HS), R21.2, R22.1
PH_V_HO: R21.1, U7.43
PH_V_LG: Q3.4 (G_LS), R23.2, R24.1
PH_V_LO: R23.1, U7.42
PH_V_LSS: R28.1, U7.41
PH_V_SNS: Q3.5 (GND), Q3.6 (GND), R24.2, R25.1, R27.2, R28.2
PH_V_SNSM: R26.1, U7.6
PH_V_SNSP: R27.1, U7.5
PH_V_VB: C38.1, U7.45
PH_W: C40.2, J1.10 (W), J1.20 (W), Q4.2 (PH), Q4.3 (PH), Q4.10 (PH), R31.2, U7.47
PH_W_HG: Q4.1 (G_HS), R30.2, R31.1
PH_W_HO: R30.1, U7.48
PH_W_LG: Q4.4 (G_LS), R32.2, R33.1
PH_W_LO: R32.1, U7.1
PH_W_LSS: R37.1, U7.2
PH_W_SNS: Q4.5 (GND), Q4.6 (GND), R33.2, R34.1, R36.2, R37.2
PH_W_SNSM: R35.1, U7.8
PH_W_SNSP: R36.1, U7.7
PH_W_VB: C40.1, U7.46
PORST: R8.1, U4.97 (PORST), U5.1 (RESET)
SPARE_AIN: C53.1, D8.3 (K1/A2), R51.2, U4.39 (AN17)
SPARE_AIN_IN: D11.1 (K1), D11.2 (K2), J1.15 (SPARE_AIN), R51.1
SPARE_PWM: R52.1, U4.14 (P00.3)
SPARE_PWM_OUT: C54.1, D9.2 (K2), J1.6 (SPARE_PWM), R52.2
TCK: J2.3 (TCK), U4.92 (TCK)
TEMP: C52.1, R50.2, RT1.1, U4.38 (AN20)
TMS: J2.2 (TMS), U4.89 (TMS)
VDD: C19.1, C20.1, C21.1, U4.10 (VDD), U4.22 (VDD), U4.72 (VDD), U4.79 (VDD), U4.99 (VDD), U4.127 (VDD)
VIN_PG: D1.2 (A), Q1.1 (G), R1.1
VIN_RAW: J1.1 (BAT), J1.11 (BAT), Q1.4 (D)
VMON: C51.1, R48.2, R49.1, U4.37 (AN21)
WDI: U4.56 (P33.0), U5.4 (WDI)
XTAL1: C23.1, U4.81 (XTAL1), Y1.1
XTAL2: C24.1, U4.82 (XTAL2), Y1.3
